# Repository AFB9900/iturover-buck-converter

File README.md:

# 42 V → 24 V / 12 V Buck Dönüştürücü Kartı

İTÜ Rover Elektronik Ekibi '25 dönemi devre tasarımı ödevi (Devre Örneği 1). 10S Li-ion bataryadan (30–42 V) gelen gerilimi iki ayrı LT8648S ile 24 V ve 12 V'a düşüren, her çıkıştan 5 A verebilen dört katmanlı güç kartı. KiCad 9 ile tasarlandı, LTspice ile simüle edildi.

## Özellikler

| | |
|---|---|
| Giriş | 30–42 V (10S Li-ion), XT60 |
| Çıkışlar | 24 V / 5 A ve 12 V / 5 A, XT30 |
| Regülatör | 2 × Analog Devices LT8648S (Silent Switcher 2), 1 MHz |
| İndüktör | 4,7 µH Coilcraft XAL1010-472ME (iki çıkışta aynı) |
| Korumalar | 10 A ATO sigorta, P-MOSFET ile ters polarite koruması, SMCJ43A TVS, 100 µF bulk kondansatör, 27,8 V'ta açılıp 26,7 V'ta kapanan düşük gerilim kilidi |
| Kart | 100 × 75 mm, 4 katman (iç katmanlar kesintisiz GND) |
| Diğer | Her çıkışta durum LED'i, PG sinyali ve test noktaları |

## Simülasyon sonuçları (V_IN = 42 V, tam yük)

| | 24 V ray | 12 V ray |
|---|---|---|
| Ortalama çıkış | 23,96 V | 12,04 V |
| Çıkış dalgalanması (tepe-tepe) | 9,1 mV | 4,5 mV |
| İndüktör dalgalanma akımı (hesap / simülasyon) | 2,19 A / 2,16 A | 1,82 A / 1,80 A |
| Açılış süresi | ≈ 4 ms, aşırı yükselme yok | ≈ 4 ms, aşırı yükselme yok |

## Klasörler

| Klasör | İçerik |
|---|---|
| `KiCad_Proje/` | KiCad 9 projesi: hiyerarşik şematik (giriş koruması, 24 V, 12 V), kart dosyası, proje kütüphaneleri (`Lib/`) ve DRC raporu |
| `Uretim_Dosyalari/` | Gerber, drill, job dosyası ve BOM |
| `Simulasyon/` | LTspice devreleri (`.asc`) ve sonuç grafikleri |
| `Gorseller/` | Şematik PDF ve kart görselleri |
| `Rapor_AhmetFurkanBilgin.pdf` | Açık uçlu sorular, bileşen seçimi, hesaplamalar, simülasyon, riskler ve alternatifler |

## Projeyi açmak

`KiCad_Proje/BuckConvertor.kicad_pro` dosyasını KiCad 9 ile aç. Sembol ve footprint kütüphaneleri proje klasöründeki `Lib/` içinde, `${KIPRJMOD}` üzerinden bağlı; ek kurulum gerekmez.

Simülasyon için `Simulasyon/` içindeki `.asc` dosyalarını LTspice ile aç ve çalıştır (`.tran 7m startup`).

## Bilinen sınırlar

- LT8648S'nin maksimum giriş gerilimi 42 V, tam dolu 10S paket de 42 V veriyor; giriş payı yok. Ayrıntı ve alternatifler raporun 2.7 ve 2.8 bölümlerinde.
- 24 V entegresi tam yükte belirgin şekilde ısınır (tahmini 6–9 W kayıp).
- Yük basamağı ve düşük gerilim kilidi henüz simüle edilmedi.

Hazırlayan: Ahmet Furkan Bilgin

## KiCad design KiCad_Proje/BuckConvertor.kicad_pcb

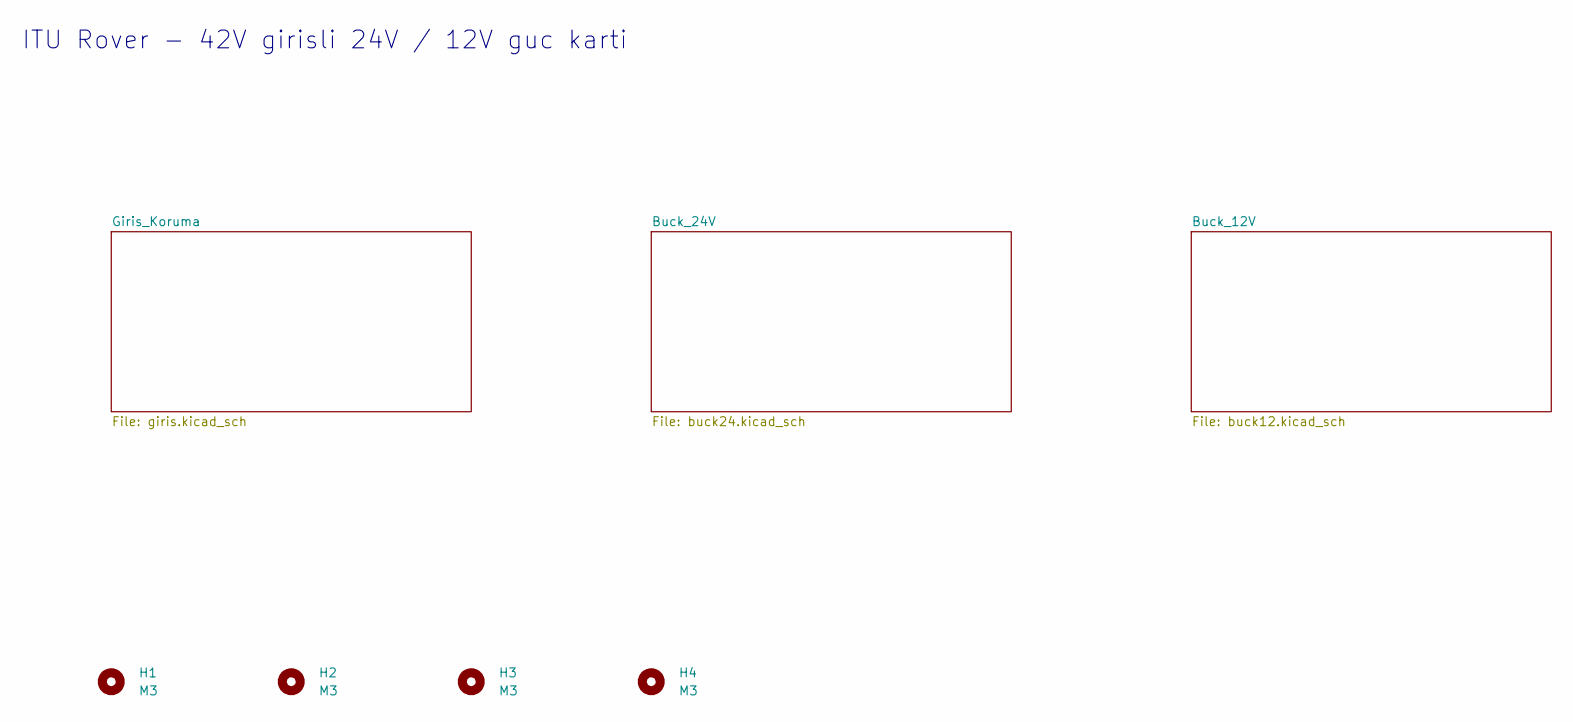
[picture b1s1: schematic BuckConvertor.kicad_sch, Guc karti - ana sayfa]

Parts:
H1, H2, H3, H4: M3; MountingHole_3.2mm_M3

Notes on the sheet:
ITU Rover - 42V girisli 24V / 12V guc karti

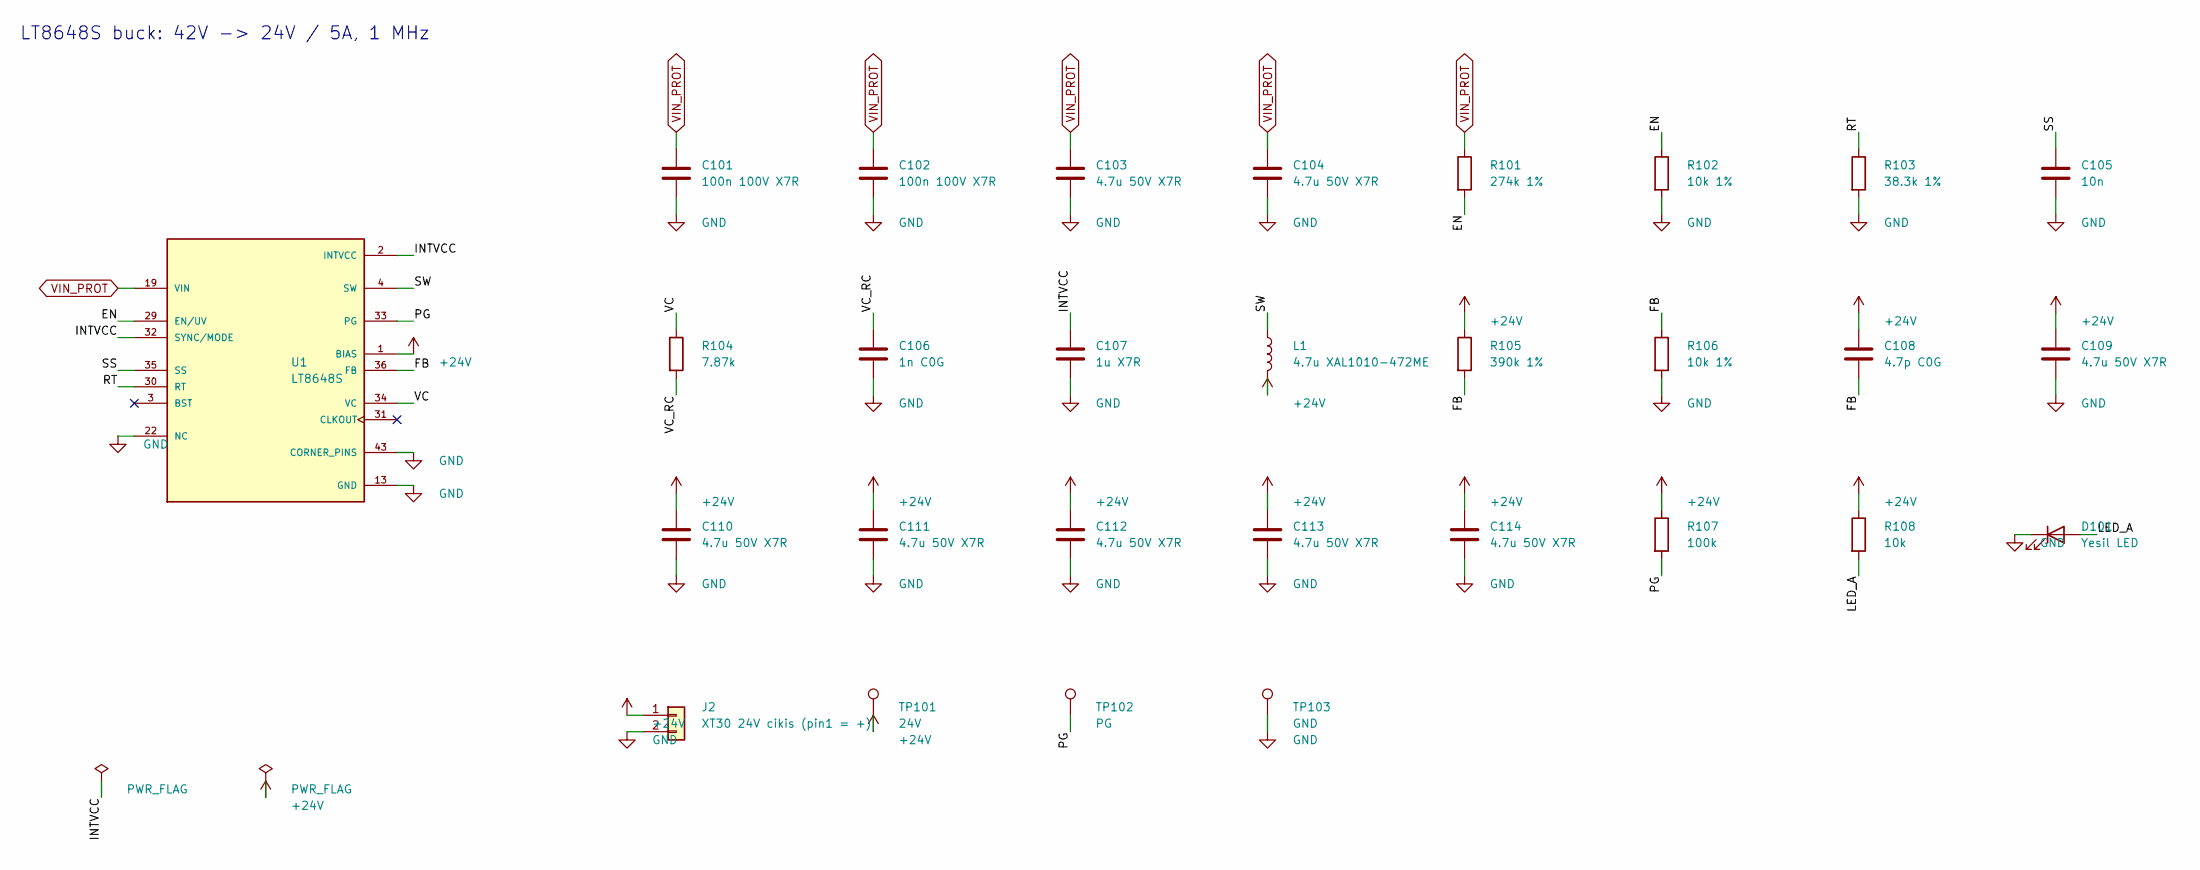
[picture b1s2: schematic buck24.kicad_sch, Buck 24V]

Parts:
C101, C102: 100n 100V X7R; C_0603_1608Metric
C103, C104, C109, C110, C111, C112, C113, C114: 4.7u 50V X7R; C_1210_3225Metric
C105: 10n; C_0805_2012Metric
C106: 1n C0G; C_0805_2012Metric
C107: 1u X7R; C_0805_2012Metric
C108: 4.7p C0G; C_0805_2012Metric
D101: Yesil LED; LED_0805_2012Metric
J2: XT30 24V cikis (pin1 = +); AMASS_XT30U-F_1x02_P5.0mm_Vertical
L1: 4.7u XAL1010-472ME; L_Coilcraft_XAL1010-XXX
R101: 274k 1%; R_0805_2012Metric
R102, R106: 10k 1%; R_0805_2012Metric
R103: 38.3k 1%; R_0805_2012Metric
R104: 7.87k; R_0805_2012Metric
R105: 390k 1%; R_0805_2012Metric
R107: 100k; R_0805_2012Metric
R108: 10k; R_0805_2012Metric
TP101: 24V; TestPoint_Pad_D1.5mm
TP102: PG; TestPoint_Pad_D1.5mm
TP103: GND; TestPoint_Pad_D1.5mm
U1: LT8648S; IC_LT8648SEV_TRPBF; MPN LT8648SEV#TRPBF

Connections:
+24V: C108.1, C109.1, C110.1, C111.1, C112.1, C113.1, C114.1, J2.1, L1.2, R105.1, R107.1, R108.1, TP101.1, U1.1 (BIAS)
/Buck_24V/EN: R101.2, R102.1, U1.29 (EN/UV)
/Buck_24V/FB: C108.2, R105.2, R106.1, U1.36 (FB)
/Buck_24V/INTVCC: C107.1, U1.2 (INTVCC), U1.32 (SYNC/MODE)
/Buck_24V/LED_A: D101.2 (A), R108.2
/Buck_24V/PG: R107.2, TP102.1, U1.33 (PG)
/Buck_24V/RT: R103.1, U1.30 (RT)
/Buck_24V/SS: C105.1, U1.35 (SS)
/Buck_24V/SW: L1.1, U1.4 (SW), U1.5 (SW), U1.6 (SW), U1.7 (SW), U1.8 (SW), U1.9 (SW), U1.10 (SW), U1.11 (SW), U1.12 (SW)
/Buck_24V/VC: R104.1, U1.34 (VC)
/Buck_24V/VC_RC: C106.1, R104.2
GND: C101.2, C102.2, C103.2, C104.2, C105.2, C106.2, C107.2, C109.2, C110.2, C111.2, C112.2, C113.2, C114.2, D101.1 (K), J2.2, R102.2, R103.2, R106.2, TP103.1, U1.13 (GND), U1.14 (GND), U1.15 (GND), U1.16 (GND), U1.17 (GND), U1.18 (GND), U1.22 (NC), U1.23 (GND), U1.24 (GND), U1.25 (NC), U1.37 (GND), U1.38 (GND), U1.39 (GND), U1.40 (GND), U1.41 (GND), U1.42 (GND), U1.43 (CORNER_PINS), U1.44 (CORNER_PINS), U1.45 (CORNER_PINS), U1.46 (CORNER_PINS); also elsewhere on the board
VIN_PROT: C101.1, C102.1, C103.1, C104.1, R101.1, U1.19 (VIN), U1.20 (VIN), U1.21 (VIN), U1.26 (VIN), U1.27 (VIN), U1.28 (VIN); also elsewhere on the board

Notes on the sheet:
LT8648S buck: 42V -> 24V / 5A, 1 MHz

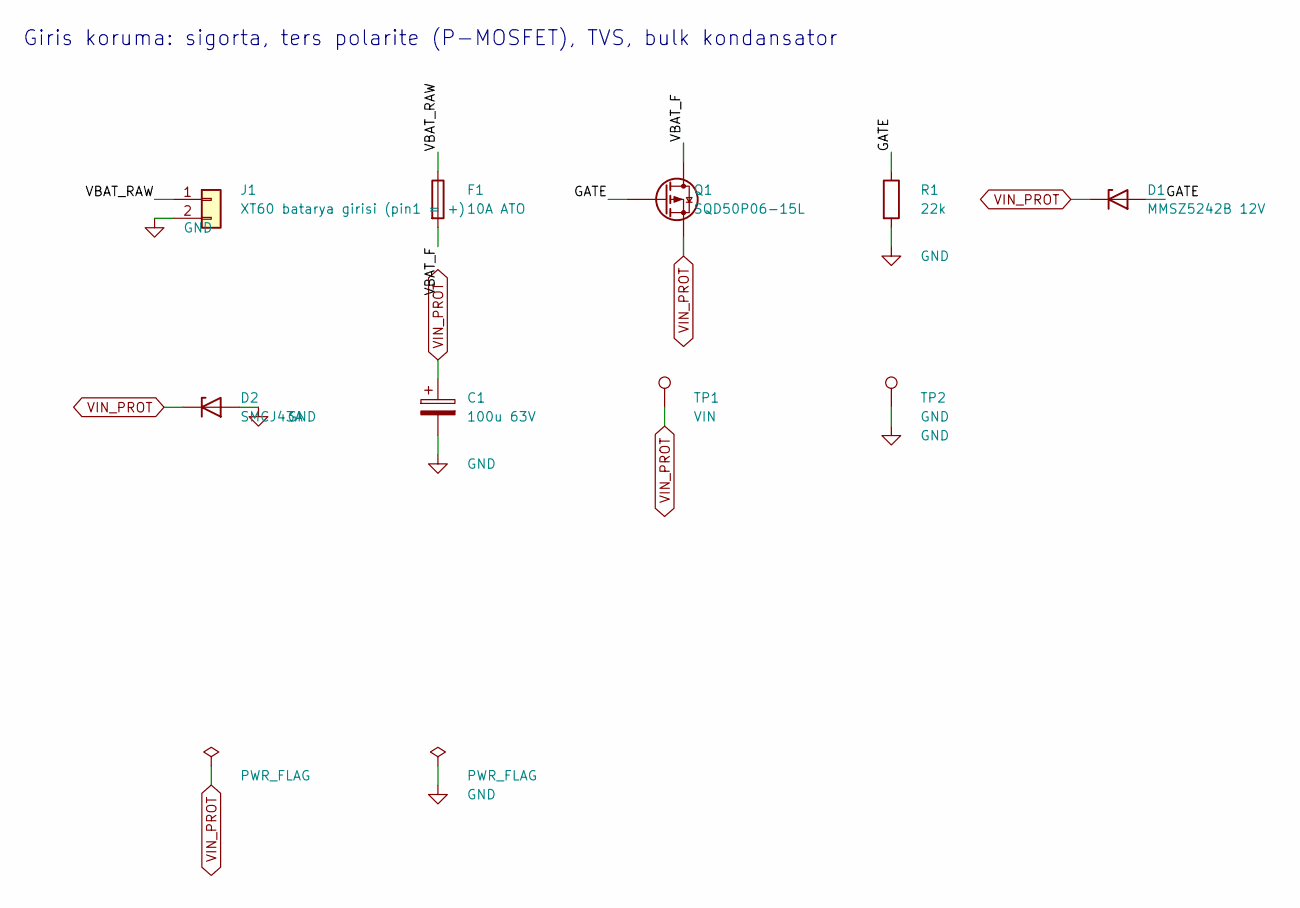
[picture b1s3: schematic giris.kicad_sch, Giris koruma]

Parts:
C1: 100u 63V; CP_Radial_D10.0mm_P5.00mm
D1: MMSZ5242B 12V; D_SOD-123
D2: SMCJ43A; D_SMC
F1: 10A ATO; FuseHolder_Blade_ATO_Littelfuse_FLR_178.6165
J1: XT60 batarya girisi (pin1 = +); AMASS_XT60-M_1x02_P7.20mm_Vertical
Q1: SQD50P06-15L; TO-252-2
R1: 22k; R_0805_2012Metric
TP1: VIN; TestPoint_Pad_D1.5mm
TP2: GND; TestPoint_Pad_D1.5mm

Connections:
/Giris_Koruma/GATE: D1.2 (A), Q1.1 (G), R1.1
/Giris_Koruma/VBAT_F: F1.2, Q1.2 (D)
/Giris_Koruma/VBAT_RAW: F1.1, J1.1
GND: C1.2, D2.2 (A), J1.2, R1.2, TP2.1; also elsewhere on the board
VIN_PROT: C1.1, D1.1 (K), D2.1 (K), Q1.3 (S), TP1.1; also elsewhere on the board

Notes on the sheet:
Giris koruma: sigorta, ters polarite (P-MOSFET), TVS, bulk kondansator

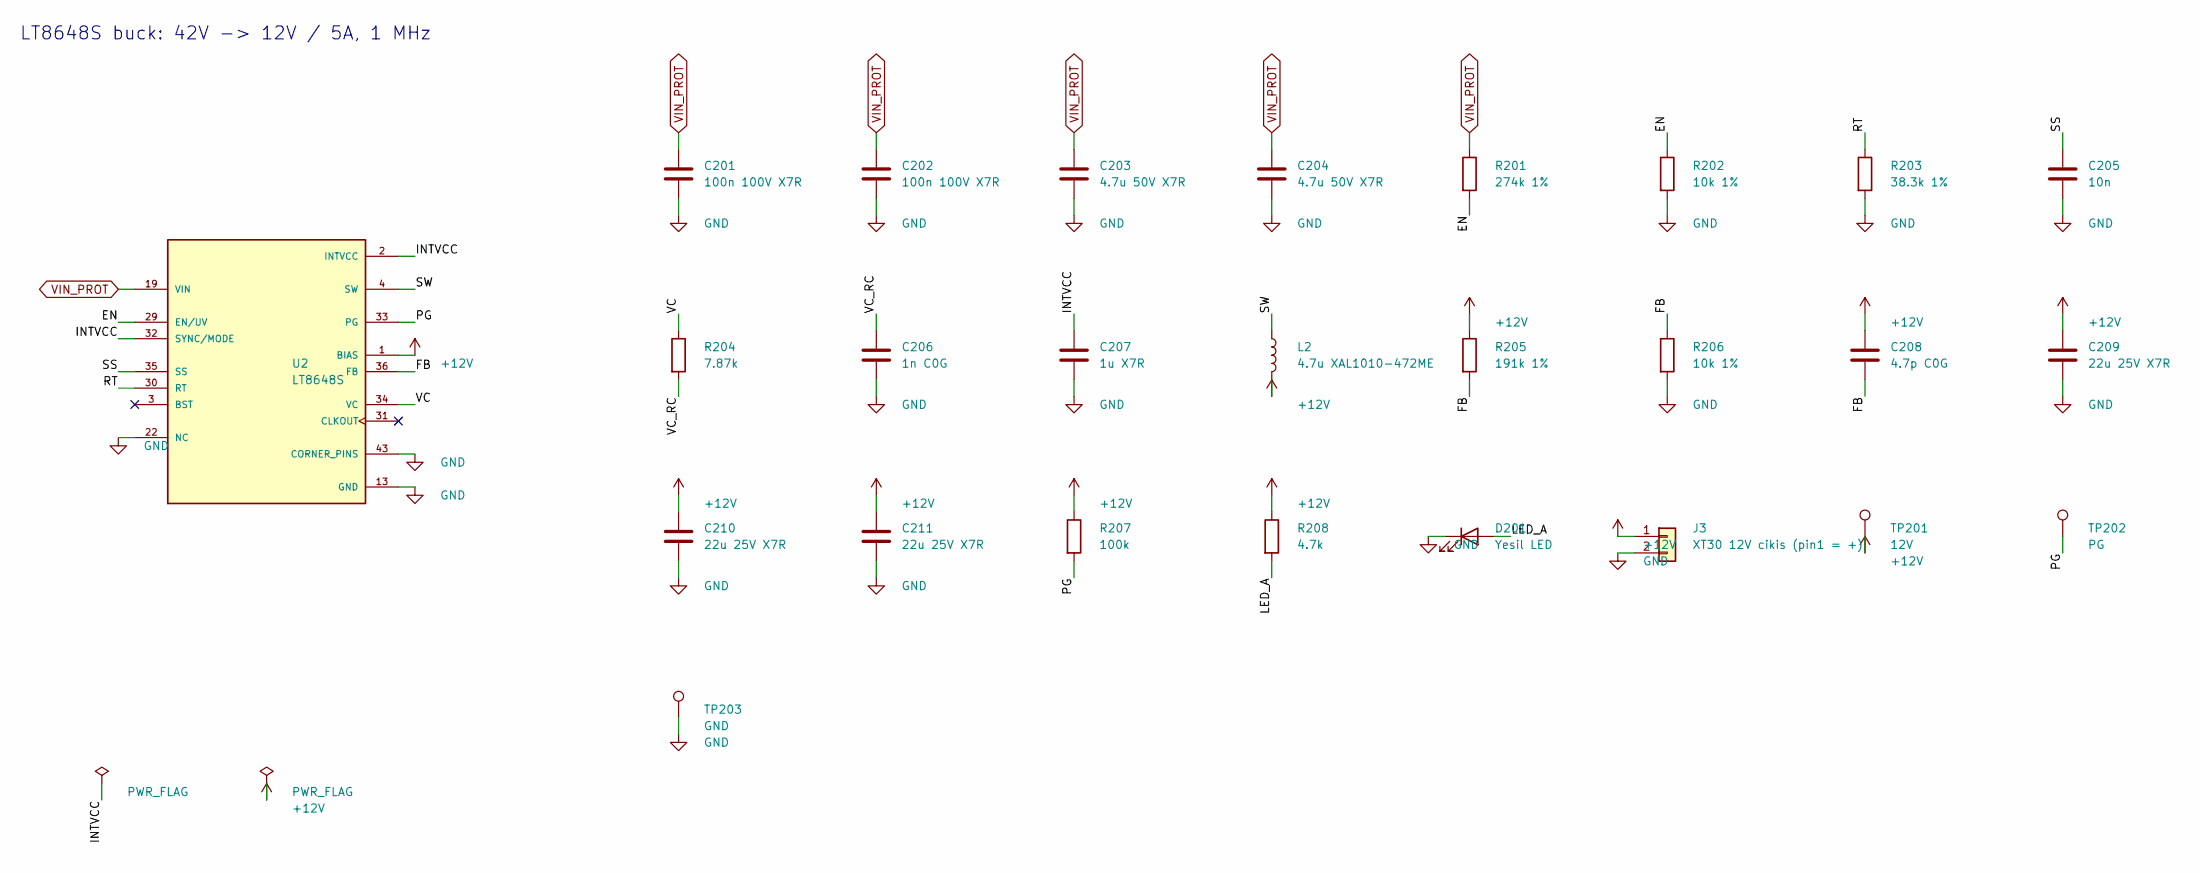
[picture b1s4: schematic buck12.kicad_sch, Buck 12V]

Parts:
C201, C202: 100n 100V X7R; C_0603_1608Metric
C203, C204: 4.7u 50V X7R; C_1210_3225Metric
C205: 10n; C_0805_2012Metric
C206: 1n C0G; C_0805_2012Metric
C207: 1u X7R; C_0805_2012Metric
C208: 4.7p C0G; C_0805_2012Metric
C209, C210, C211: 22u 25V X7R; C_1210_3225Metric
D201: Yesil LED; LED_0805_2012Metric
J3: XT30 12V cikis (pin1 = +); AMASS_XT30U-F_1x02_P5.0mm_Vertical
L2: 4.7u XAL1010-472ME; L_Coilcraft_XAL1010-XXX
R201: 274k 1%; R_0805_2012Metric
R202, R206: 10k 1%; R_0805_2012Metric
R203: 38.3k 1%; R_0805_2012Metric
R204: 7.87k; R_0805_2012Metric
R205: 191k 1%; R_0805_2012Metric
R207: 100k; R_0805_2012Metric
R208: 4.7k; R_0805_2012Metric
TP201: 12V; TestPoint_Pad_D1.5mm
TP202: PG; TestPoint_Pad_D1.5mm
TP203: GND; TestPoint_Pad_D1.5mm
U2: LT8648S; IC_LT8648SEV_TRPBF; MPN LT8648SEV#TRPBF

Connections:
+12V: C208.1, C209.1, C210.1, C211.1, J3.1, L2.2, R205.1, R207.1, R208.1, TP201.1, U2.1 (BIAS)
/Buck_12V/EN: R201.2, R202.1, U2.29 (EN/UV)
/Buck_12V/FB: C208.2, R205.2, R206.1, U2.36 (FB)
/Buck_12V/INTVCC: C207.1, U2.2 (INTVCC), U2.32 (SYNC/MODE)
/Buck_12V/LED_A: D201.2 (A), R208.2
/Buck_12V/PG: R207.2, TP202.1, U2.33 (PG)
/Buck_12V/RT: R203.1, U2.30 (RT)
/Buck_12V/SS: C205.1, U2.35 (SS)
/Buck_12V/SW: L2.1, U2.4 (SW), U2.5 (SW), U2.6 (SW), U2.7 (SW), U2.8 (SW), U2.9 (SW), U2.10 (SW), U2.11 (SW), U2.12 (SW)
/Buck_12V/VC: R204.1, U2.34 (VC)
/Buck_12V/VC_RC: C206.1, R204.2
GND: C201.2, C202.2, C203.2, C204.2, C205.2, C206.2, C207.2, C209.2, C210.2, C211.2, D201.1 (K), J3.2, R202.2, R203.2, R206.2, TP203.1, U2.13 (GND), U2.14 (GND), U2.15 (GND), U2.16 (GND), U2.17 (GND), U2.18 (GND), U2.22 (NC), U2.23 (GND), U2.24 (GND), U2.25 (NC), U2.37 (GND), U2.38 (GND), U2.39 (GND), U2.40 (GND), U2.41 (GND), U2.42 (GND), U2.43 (CORNER_PINS), U2.44 (CORNER_PINS), U2.45 (CORNER_PINS), U2.46 (CORNER_PINS); also elsewhere on the board
VIN_PROT: C201.1, C202.1, C203.1, C204.1, R201.1, U2.19 (VIN), U2.20 (VIN), U2.21 (VIN), U2.26 (VIN), U2.27 (VIN), U2.28 (VIN); also elsewhere on the board

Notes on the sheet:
LT8648S buck: 42V -> 12V / 5A, 1 MHz

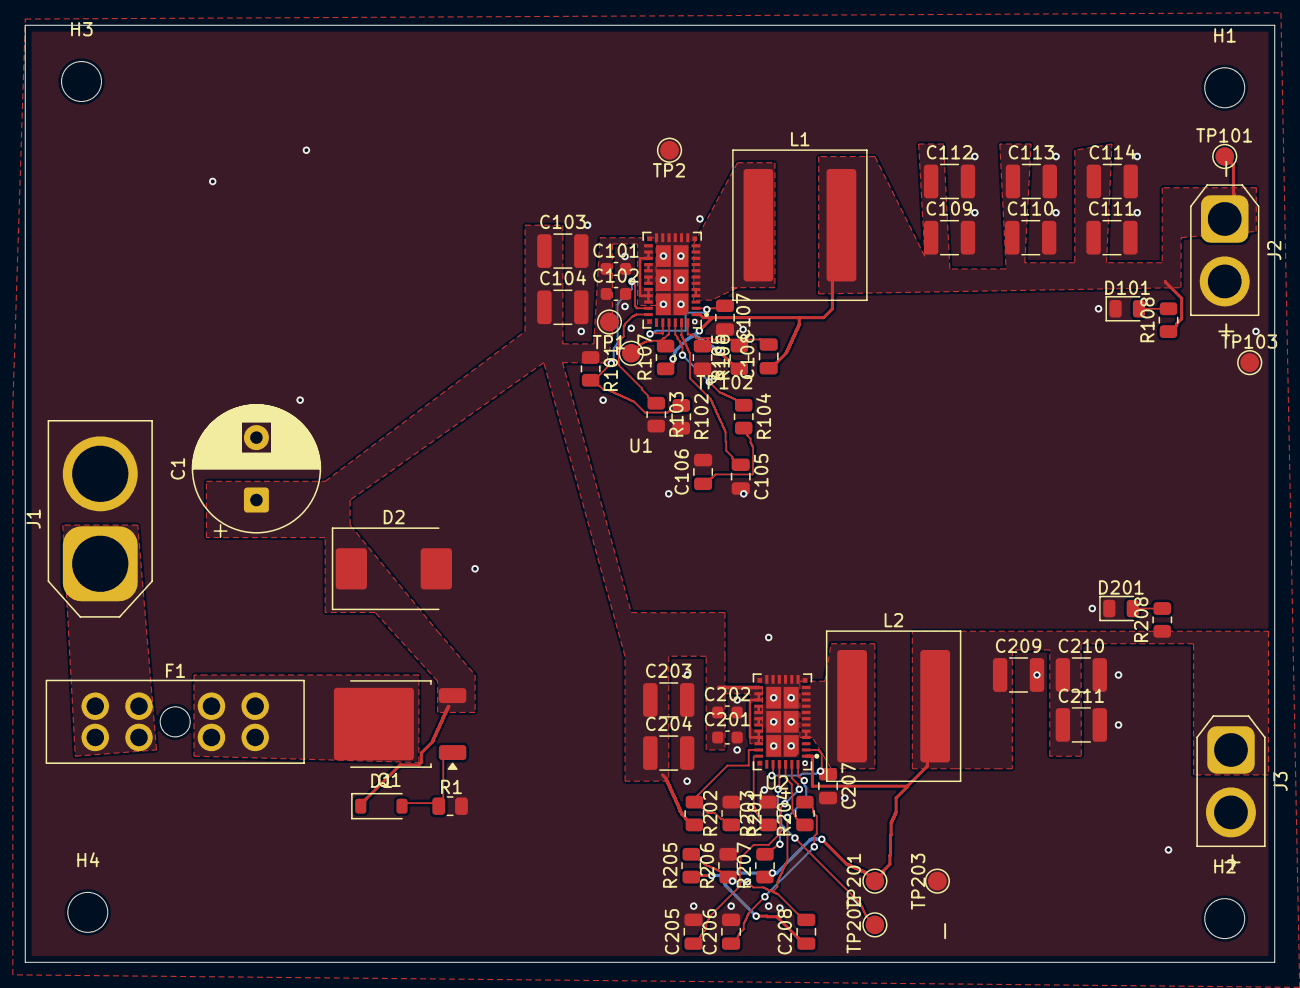
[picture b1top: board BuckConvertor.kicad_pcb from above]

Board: 4 copper layers, 100.0 x 75.0 mm, 68 parts (0 on the bottom side), 27 nets.

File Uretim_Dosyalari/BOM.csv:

"Reference","Qty","Value","DNP","Exclude from BOM","Exclude from Board","Footprint","Datasheet"
"C1","1","100u 63V","","","","Capacitor_THT:CP_Radial_D10.0mm_P5.00mm","~"
"C101,C102,C201,C202","4","100n 100V X7R","","","","Capacitor_SMD:C_0603_1608Metric","~"
"C103,C104,C109,C110,C111,C112,C113,C114,C203,C204","10","4.7u 50V X7R","","","","Capacitor_SMD:C_1210_3225Metric","~"
"C105,C205","2","10n","","","","Capacitor_SMD:C_0805_2012Metric","~"
"C106,C206","2","1n C0G","","","","Capacitor_SMD:C_0805_2012Metric","~"
"C107,C207","2","1u X7R","","","","Capacitor_SMD:C_0805_2012Metric","~"
"C108,C208","2","4.7p C0G","","","","Capacitor_SMD:C_0805_2012Metric","~"
"C209,C210,C211","3","22u 25V X7R","","","","Capacitor_SMD:C_1210_3225Metric","~"
"D1","1","MMSZ5242B 12V","","","","Diode_SMD:D_SOD-123","~"
"D2","1","SMCJ43A","","","","Diode_SMD:D_SMC","~"
"D101,D201","2","Yesil LED","","","","LED_SMD:LED_0805_2012Metric","~"
"F1","1","10A ATO","","","","Fuse:FuseHolder_Blade_ATO_Littelfuse_FLR_178.6165","~"
"H1,H2,H3,H4","4","M3","","","","MountingHole:MountingHole_3.2mm_M3","~"
"J1","1","XT60 batarya girisi (pin1 = +)","","","","Connector_AMASS:AMASS_XT60-M_1x02_P7.20mm_Vertical","~"
"J2","1","XT30 24V cikis (pin1 = +)","","","","Connector_AMASS:AMASS_XT30U-F_1x02_P5.0mm_Vertical","~"
"J3","1","XT30 12V cikis (pin1 = +)","","","","Connector_AMASS:AMASS_XT30U-F_1x02_P5.0mm_Vertical","~"
"L1,L2","2","4.7u XAL1010-472ME","","","","Inductor_SMD:L_Coilcraft_XAL1010-XXX","~"
"Q1","1","SQD50P06-15L","","","","Package_TO_SOT_SMD:TO-252-2","~"
"R1","1","22k","","","","Resistor_SMD:R_0805_2012Metric","~"
"R101,R201","2","274k 1%","","","","Resistor_SMD:R_0805_2012Metric","~"
"R102,R106,R202,R206","4","10k 1%","","","","Resistor_SMD:R_0805_2012Metric","~"
"R103,R203","2","38.3k 1%","","","","Resistor_SMD:R_0805_2012Metric","~"
"R104,R204","2","7.87k","","","","Resistor_SMD:R_0805_2012Metric","~"
"R105","1","390k 1%","","","","Resistor_SMD:R_0805_2012Metric","~"
"R107,R207","2","100k","","","","Resistor_SMD:R_0805_2012Metric","~"
"R108","1","10k","","","","Resistor_SMD:R_0805_2012Metric","~"
"R205","1","191k 1%","","","","Resistor_SMD:R_0805_2012Metric","~"
"R208","1","4.7k","","","","Resistor_SMD:R_0805_2012Metric","~"
"TP1","1","VIN","","","","TestPoint:TestPoint_Pad_D1.5mm","~"
"TP2,TP103,TP203","3","GND","","","","TestPoint:TestPoint_Pad_D1.5mm","~"
"TP101","1","24V","","","","TestPoint:TestPoint_Pad_D1.5mm","~"
"TP102,TP202","2","PG","","","","TestPoint:TestPoint_Pad_D1.5mm","~"
"TP201","1","12V","","","","TestPoint:TestPoint_Pad_D1.5mm","~"
"U1,U2","2","LT8648S","","","","LT8648S:IC_LT8648SEV_TRPBF","https://s3.amazonaws.com/snapeda/datasheet/LT8648SEV_TRPBF_A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"
